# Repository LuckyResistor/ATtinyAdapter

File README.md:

# ATtinyAdapter

These are the files for the ATtiny programming adapter. You will find more details here:

https://luckyresistor.me/2017/02/25/a-versatile-attiny-programming-adapter

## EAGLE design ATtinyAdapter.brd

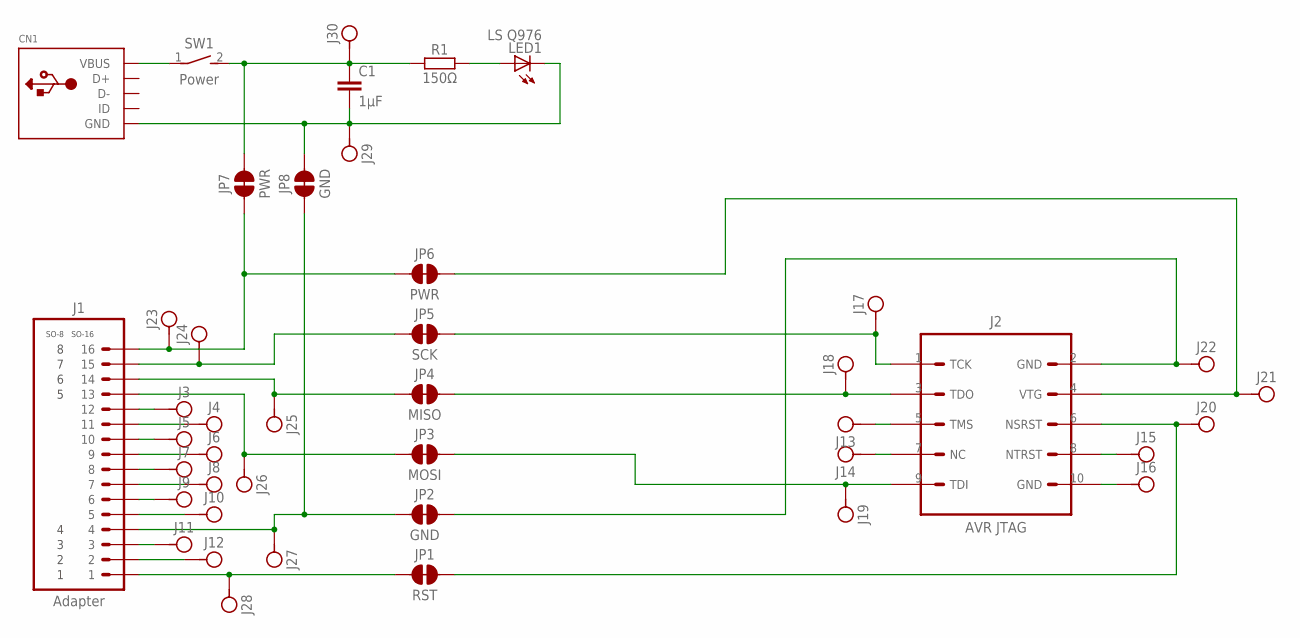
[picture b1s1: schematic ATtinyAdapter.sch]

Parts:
C1: 1µF; RESISTOR_0805
CN1: USBMINIB; USB-MINIB-HSUAN-MAO-C8320-05BFDIB0R
J1: Adapter; ELNEC-ZIF-ADAPTER-16P
J2: AVR JTAG; CON-2X5-HARWIN-1.27
J3, J4, J5, J6, J7, J8, J9, J10, J11, J12, J13, J14, J15, J16, J17, J18, J19, J20, J21, J22, J23, J24, J25, J26, J27, J28, J29, J30: CON_SOLDER_POINT
JP1: RST; JUMPER-SMD-ON
JP2, JP8: GND; JUMPER-SMD-ON
JP3: MOSI; JUMPER-SMD-ON
JP4: MISO; JUMPER-SMD-ON
JP5: SCK; JUMPER-SMD-ON
JP6, JP7: PWR; JUMPER-SMD-ON
LED1: LS Q976; CHIPLED_0603
R1: 150Ω; RESISTOR_0805
SW1: Power; SWITCH_02_3P_10.2X4.0

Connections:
JTAG1: J2.1 (TCK), J17.1, JP5.2
JTAG2: J2.2 (GND), J22.1, JP2.2
JTAG3: J2.3 (TDO), J18.1, JP4.2
JTAG4: J2.4 (VTG), J21.1, JP6.2
JTAG5: J2.5 (TMS), J13.1
JTAG6: J2.6 (NSRST), J20.1, JP1.2
JTAG7: J2.7 (NC), J14.1
JTAG8: J2.8 (NTRST), J15.1
JTAG9: J2.9 (TDI), J19.1, JP3.2
JTAG10: J2.10 (GND), J16.1
unnamed: J1.1, J28.1, JP1.1
unnamed: LED1.A, R1.2
unnamed: C1.2, CN1.GND, J29.1, JP8.2, LED1.C
unnamed: J1.16, J23.1, JP6.1, JP7.1
unnamed: CN1.VBUS, SW1.1
unnamed: J1.14, J25.1, JP4.1
unnamed: J1.15, J24.1, JP5.1
unnamed: J1.13, J26.1, JP3.1
unnamed: J1.4, J27.1, JP2.1, JP8.1
unnamed: C1.1, J30.1, JP7.2, R1.1, SW1.2 (S)
unnamed: J1.12, J3.1
unnamed: J1.11, J4.1
unnamed: J1.10, J5.1
unnamed: J1.9, J6.1
unnamed: J1.8, J7.1
unnamed: J1.7, J8.1
unnamed: J1.6, J9.1
unnamed: J1.5, J10.1
unnamed: J1.3, J11.1
unnamed: J1.2, J12.1

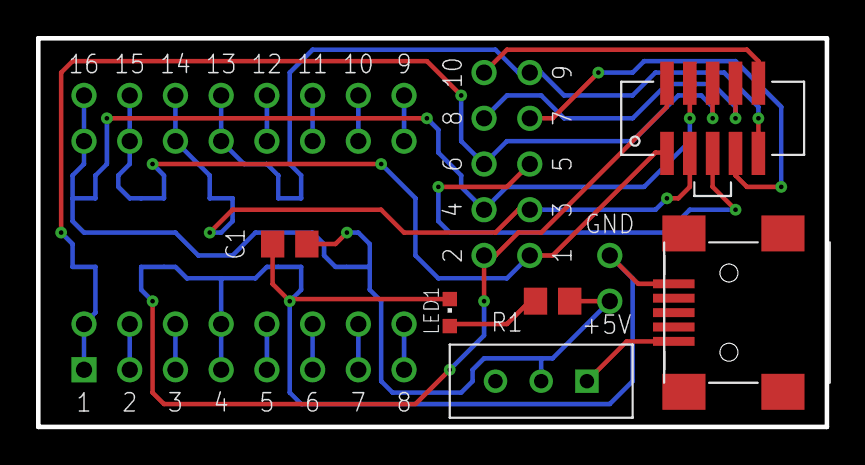
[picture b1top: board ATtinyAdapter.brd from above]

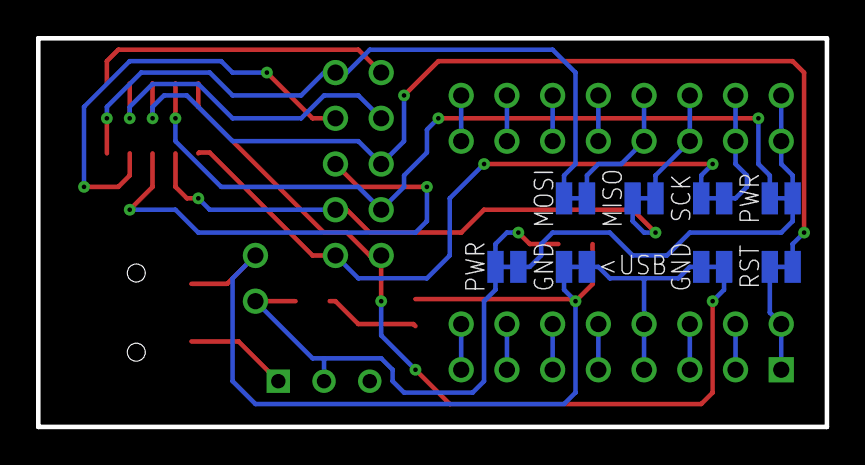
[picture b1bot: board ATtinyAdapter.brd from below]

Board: 2 copper layers, 43.8 x 21.6 mm, 43 parts (8 on the bottom side), 30 nets.

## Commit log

2017-02-25 Adding the hardware files to the repository.
2017-02-25 Add more details to the readme file.
